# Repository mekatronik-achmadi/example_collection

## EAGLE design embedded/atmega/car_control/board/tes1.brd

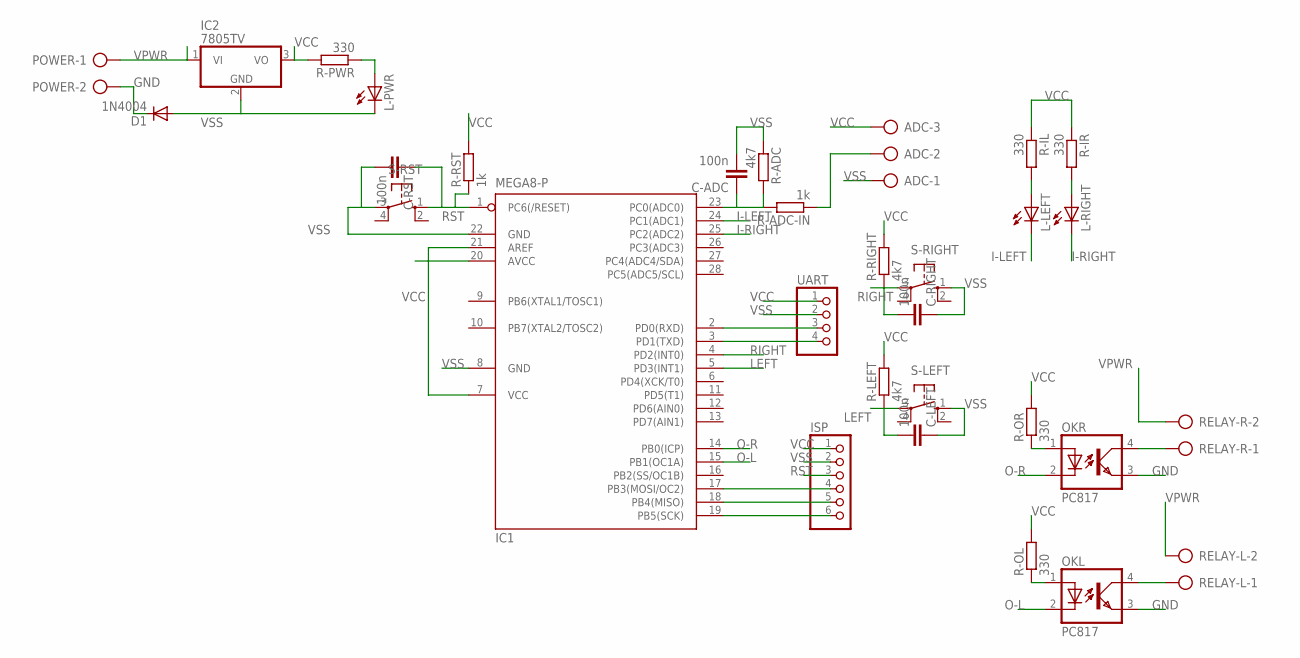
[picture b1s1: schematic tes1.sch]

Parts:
ADC: AK300/3
C-ADC: 100n; C050-024X044
C-LEFT: 100n; C050-024X044
C-RIGHT: 100n; C050-024X044
C-RST: 100n; C050-024X044
D1: 1N4004; DO41-10
IC1: MEGA8-P; DIL28-3
IC2: 7805TV; TO220V
ISP: PINHD-1X6; 1X06
L-LEFT: LED3MM
L-PWR: LED3MM
L-RIGHT: LED3MM
OKL: PC817; DIL04
OKR: PC817; DIL04
POWER: AK300/2
R-ADC: 4k7; 0204/7
R-ADC-IN: 1k; 0204/7
R-IL: 330; 0204/7
R-IR: 330; 0204/7
R-LEFT: 4k7; 0204/7
R-OL: 330; 0204/7
R-OR: 330; 0204/7
R-PWR: 330; 0204/7
R-RIGHT: 4k7; 0204/7
R-RST: 1k; 0204/7
RELAY-L: AK300/2
RELAY-R: AK300/2
S-LEFT: 10-XX; B3F-10XX
S-RIGHT: 10-XX; B3F-10XX
S-RST: 10-XX; B3F-10XX
UART: PINHD-1X4; 1X04

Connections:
GND: D1.C, OKL.3 (EMIT), OKR.3 (EMIT), POWER.2
I-LEFT: IC1.24 (PC1(ADC1)), L-LEFT.K (C)
I-RIGHT: IC1.25 (PC2(ADC2)), L-RIGHT.K (C)
LEFT: C-LEFT.2, IC1.5 (PD3(INT1)), R-LEFT.1, S-LEFT.3
unnamed: ADC.2, R-ADC-IN.1
unnamed: C-ADC.1, IC1.23 (PC0(ADC0)), R-ADC.2, R-ADC-IN.2
unnamed: IC1.3 (PD1(TXD)), UART.4
unnamed: IC1.2 (PD0(RXD)), UART.3
unnamed: L-PWR.A, R-PWR.1
unnamed: OKR.1 (A), R-OR.1
unnamed: OKL.1 (A), R-OL.1
unnamed: OKR.4 (COL), RELAY-R.1
unnamed: OKL.4 (COL), RELAY-L.1
unnamed: IC1.19 (PB5(SCK)), ISP.6
unnamed: IC1.18 (PB4(MISO)), ISP.5
unnamed: IC1.17 (PB3(MOSI/OC2)), ISP.4
unnamed: L-LEFT.A, R-IL.2
unnamed: L-RIGHT.A, R-IR.2
O-L: IC1.15 (PB1(OC1A)), OKL.2 (C)
O-R: IC1.14 (PB0(ICP)), OKR.2 (C)
RIGHT: C-RIGHT.2, IC1.4 (PD2(INT0)), R-RIGHT.1, S-RIGHT.3
RST: C-RST.1, IC1.1 (PC6(/RESET)), ISP.3, R-RST.1, S-RST.1 (S)
VCC: ADC.3, IC1.7 (VCC), IC1.20 (AVCC), IC1.21 (AREF), IC2.3 (VO), ISP.1, R-IL.1, R-IR.1, R-LEFT.2, R-OL.2, R-OR.2, R-PWR.2, R-RIGHT.2, R-RST.2, UART.1
VPWR: IC2.1 (VI), POWER.1, RELAY-L.2, RELAY-R.2
VSS: ADC.1, C-ADC.2, C-LEFT.1, C-RIGHT.1, C-RST.2, D1.A, IC1.8 (GND), IC1.22 (GND), IC2.2 (GND), ISP.2, L-PWR.K (C), R-ADC.1, S-LEFT.1 (S), S-RIGHT.1 (S), S-RST.3, UART.2

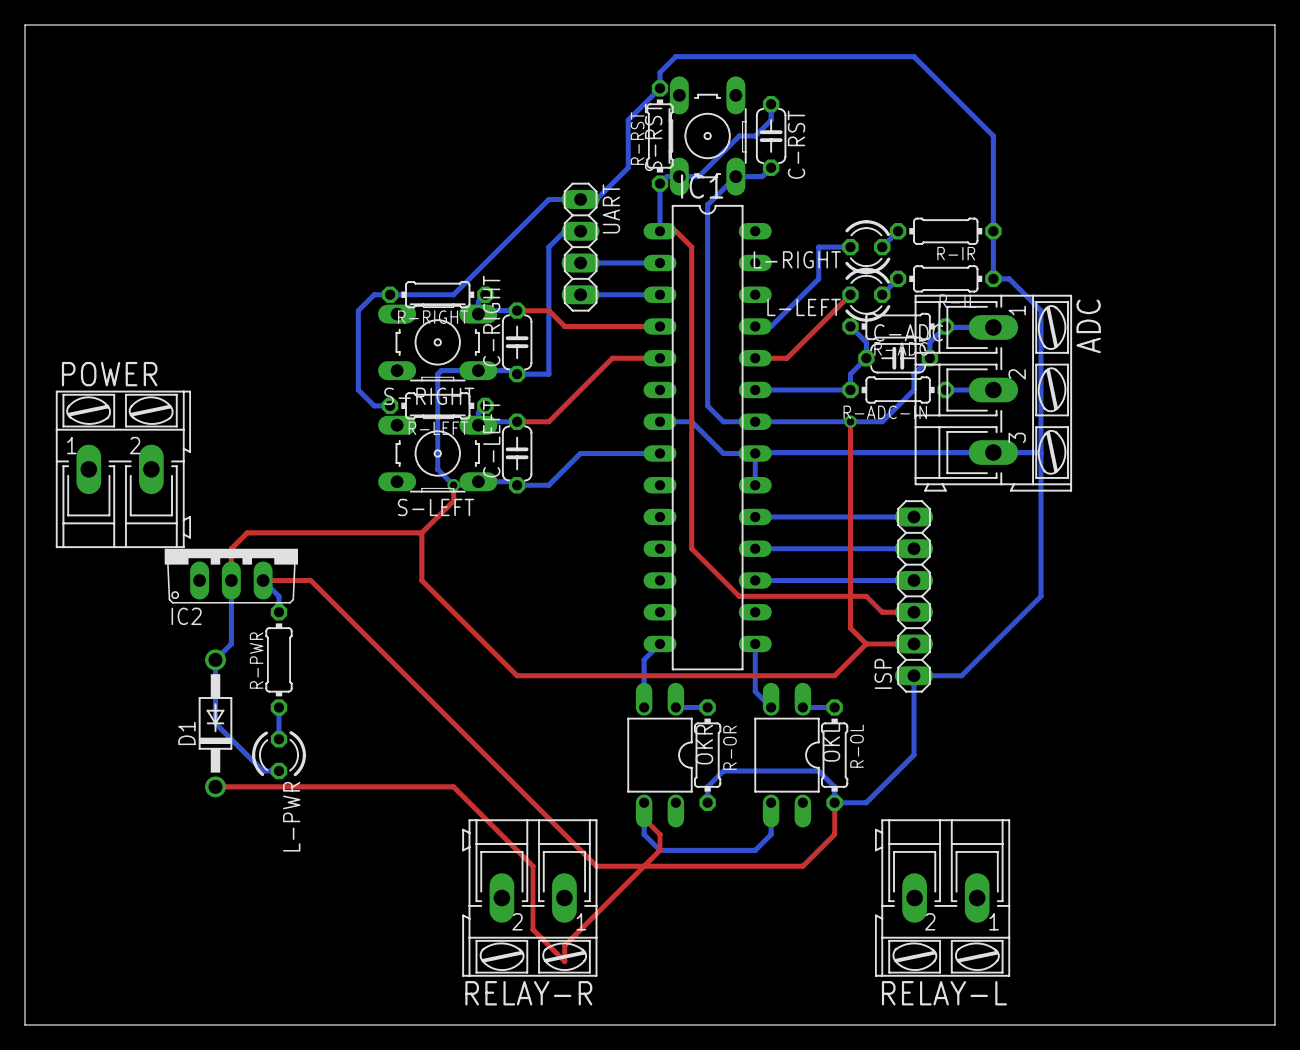
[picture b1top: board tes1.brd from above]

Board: 2 copper layers, 100.0 x 80.0 mm, 31 parts (0 on the bottom side), 25 nets.

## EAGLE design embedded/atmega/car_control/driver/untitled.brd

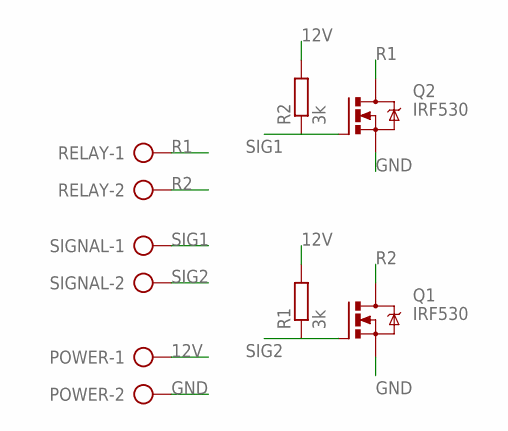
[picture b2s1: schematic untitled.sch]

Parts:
POWER: AK300/2
Q1, Q2: IRF530; TO220BV
R1, R2: 3k; 0204/7
RELAY: AK300/2
SIGNAL: AK300/2

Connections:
12V: POWER.1, R1.2, R2.2
GND: POWER.2, Q1.S, Q2.S
R1: Q2.D, RELAY.1
R2: Q1.D, RELAY.2
SIG1: Q2.G, R2.1, SIGNAL.1
SIG2: Q1.G, R1.1, SIGNAL.2

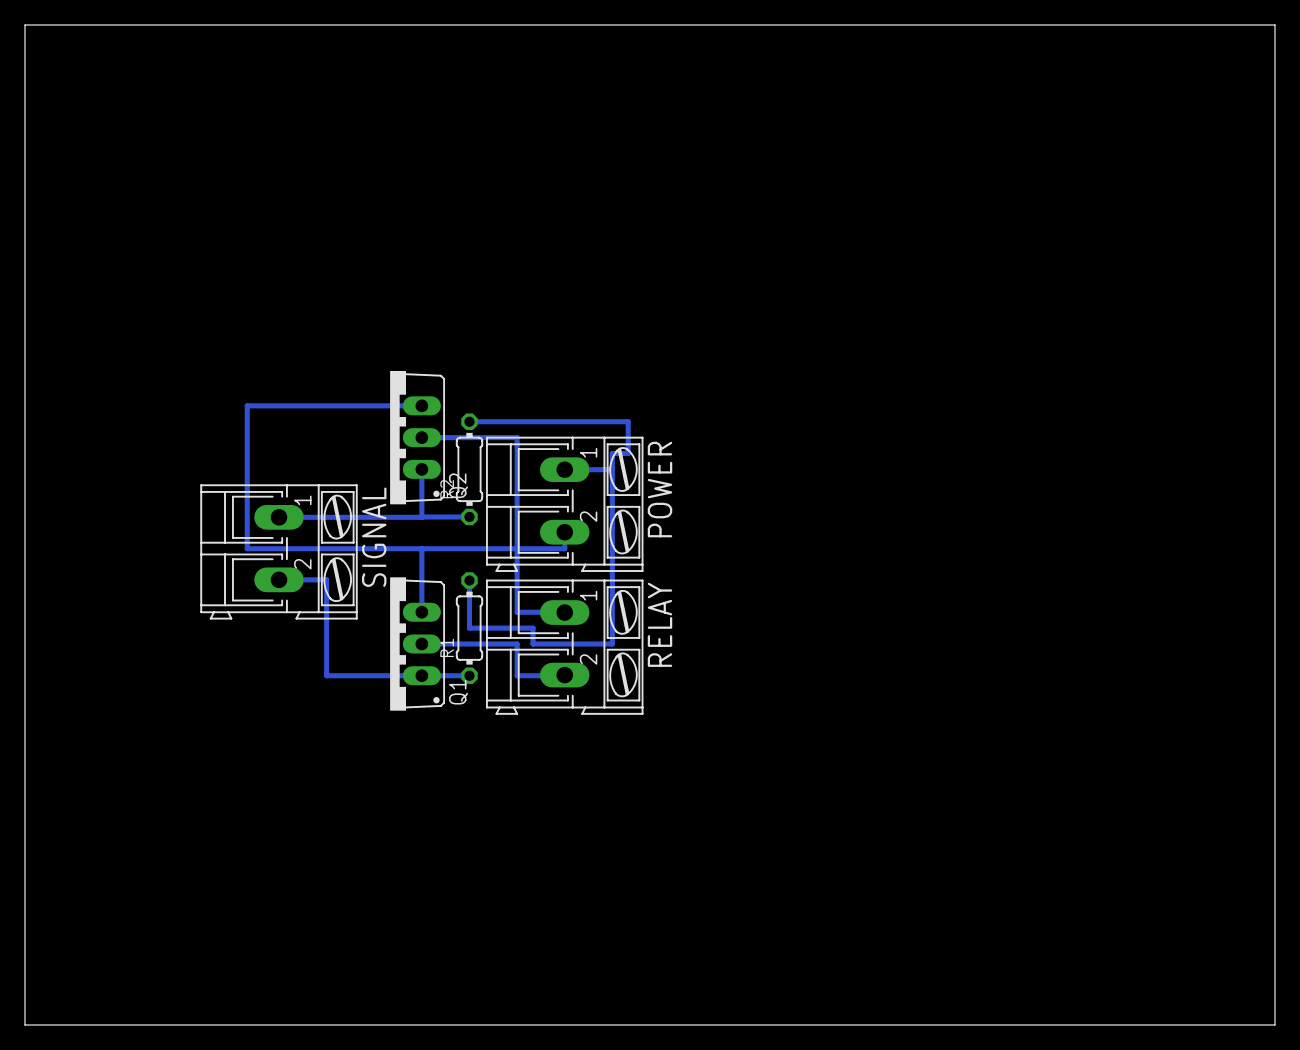
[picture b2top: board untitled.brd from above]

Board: 2 copper layers, 100.0 x 80.0 mm, 7 parts (0 on the bottom side), 6 nets.

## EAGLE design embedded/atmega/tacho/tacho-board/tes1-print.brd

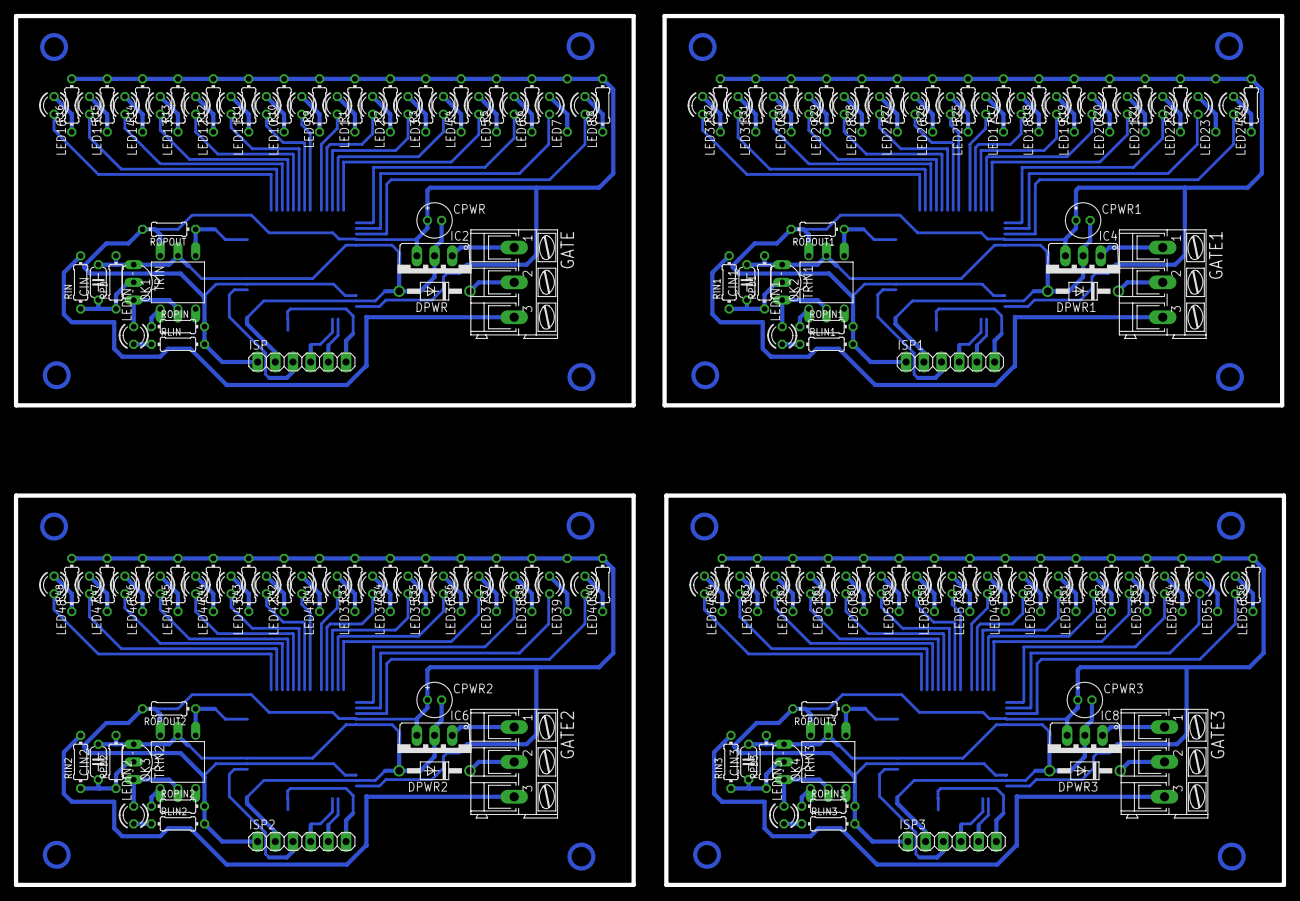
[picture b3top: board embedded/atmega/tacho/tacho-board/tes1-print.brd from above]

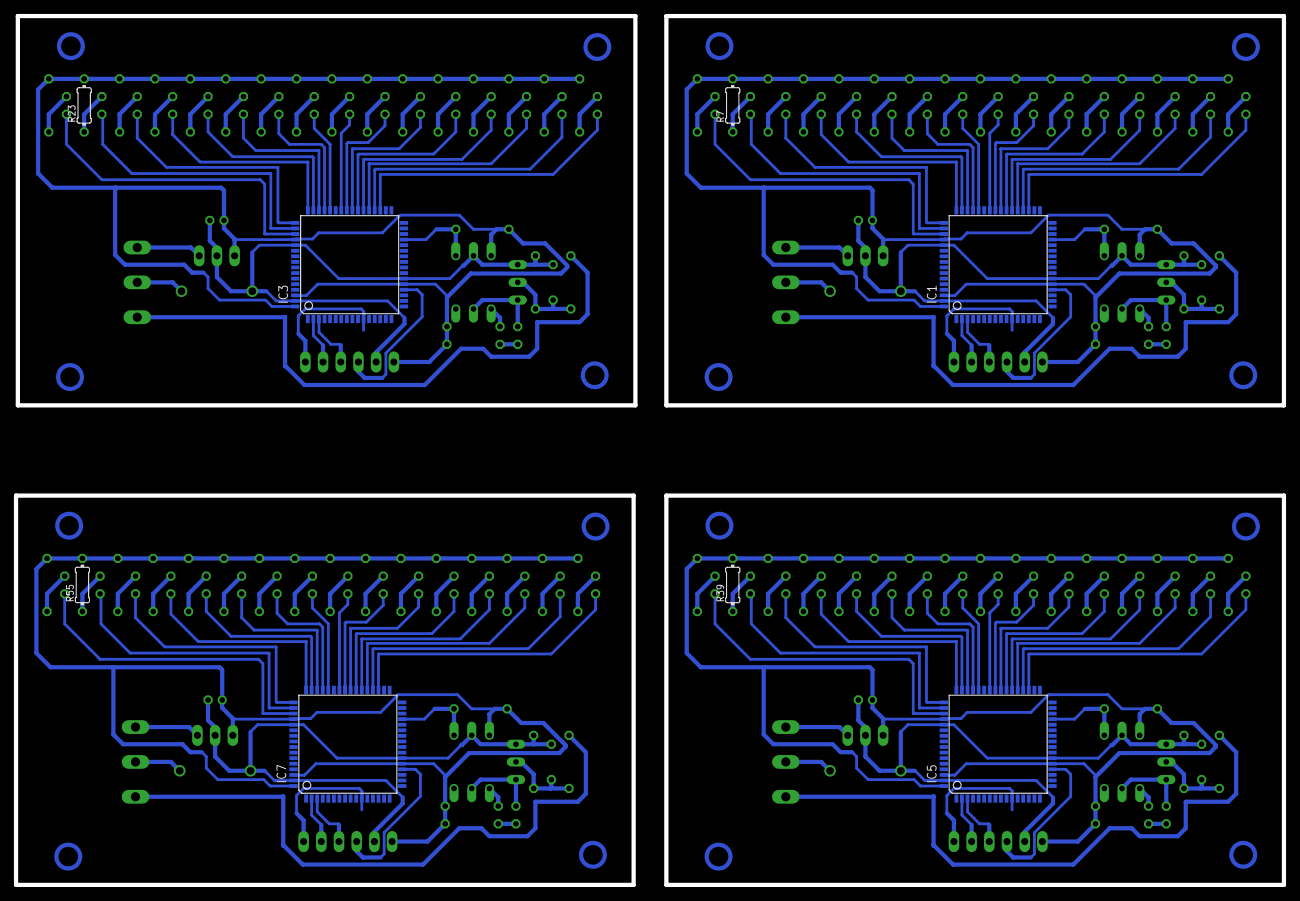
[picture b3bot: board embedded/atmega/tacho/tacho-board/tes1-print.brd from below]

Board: 2 copper layers, 182.0 x 124.7 mm, 188 parts (8 on the bottom side), 184 nets.

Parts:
CIN, CIN1, CIN2, CIN3: 100n; C050-024X044
CPWR, CPWR1, CPWR2, CPWR3: 100u; E2-5
DPWR, DPWR1, DPWR2, DPWR3: 1N4004; DO41-10
GATE, GATE1, GATE2, GATE3: AK300/3
IC1, IC3, IC5, IC7: MEGA128-A; TQFP64
IC2, IC4, IC6, IC8: 7805TV; TO220V
ISP, ISP1, ISP2, ISP3: 1X06
LED1, LED2, LED3, LED4, LED5, LED6, LED7, LED8, LED9, LED10, LED11, LED12, LED13, LED14, LED15, LED16, LED17, LED18, LED19, LED20, LED21, LED22, LED23, LED24, LED25, LED26, LED27, LED28, LED29, LED30, LED31, LED32, LED33, LED34, LED35, LED36, LED37, LED38, LED39, LED40, LED41, LED42, LED43, LED44, LED45, LED46, LED47, LED48, LED49, LED50, LED51, LED52, LED53, LED54, LED55, LED56, LED57, LED58, LED59, LED60, LED61, LED62, LED63, LED64: LED3MM
LEDIN, LEDIN1, LEDIN2, LEDIN3: LED3MM
OK1, OK2, OK3, OK4: H11L1M; DIL06
R1, R2, R3, R4, R5, R6, R7, R8, R9, R10, R11, R12, R13, R14, R15, R16, R17, R18, R19, R20, R21, R22, R23, R24, R25, R26, R27, R28, R29, R30, R31, R32, R33, R34, R35, R36, R37, R38, R39, R40, R41, R42, R43, R44, R45, R46, R47, R48, R49, R50, R51, R52, R53, R54, R55, R56, R57, R58, R59, R60, R61, R62, R63, R64: 220; 0204/7
RIN, RIN1, RIN2, RIN3: 1k; 0204/7
RLIN, RLIN1, RLIN2, RLIN3: 220; 0204/7
ROPIN, ROPIN1, ROPIN2, ROPIN3: 220; 0204/7
ROPOUT, ROPOUT1, ROPOUT2, ROPOUT3: 4k7; 0204/7
RPD, RPD1, RPD2, RPD3: 4k7; 0204/7
TRIN, TRIN1, TRIN2, TRIN3: TO92-EBC

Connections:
FIN: IC1.29, OK1.4, ROPOUT.1
FIN1: IC3.29, OK2.4, ROPOUT1.1
FIN2: IC5.29, OK3.4, ROPOUT2.1
FIN3: IC7.29, OK4.4, ROPOUT3.1
GND: CIN.2, CPWR.-, DPWR.A, IC1.22, IC1.53, IC1.63, IC2.2, ISP.2, OK1.5, RPD.2, TRIN.E
GND1: CIN1.2, CPWR1.-, DPWR1.A, IC3.22, IC3.53, IC3.63, IC4.2, ISP1.2, OK2.5, RPD1.2, TRIN1.E
GND2: CIN2.2, CPWR2.-, DPWR2.A, IC5.22, IC5.53, IC5.63, IC6.2, ISP2.2, OK3.5, RPD2.2, TRIN2.E
GND3: CIN3.2, CPWR3.-, DPWR3.A, IC7.22, IC7.53, IC7.63, IC8.2, ISP3.2, OK4.5, RPD3.2, TRIN3.E
IN: GATE.3, RIN.2
IN1: GATE1.3, RIN1.2
IN2: GATE2.3, RIN2.2
IN3: GATE3.3, RIN3.2
MISO: IC1.3, ISP.4
MISO1: IC3.3, ISP1.4
MISO2: IC5.3, ISP2.4
MISO3: IC7.3, ISP3.4
MOSI: IC1.2, ISP.5
MOSI1: IC3.2, ISP1.5
MOSI2: IC5.2, ISP2.5
MOSI3: IC7.2, ISP3.5
unnamed: LED2.A, R2.1
unnamed: LED17.A, R17.1
unnamed: LED18.A, R18.1
unnamed: LED19.A, R19.1
unnamed: LED20.A, R20.1
unnamed: LED21.A, R21.1
unnamed: LED3.A, R3.1
unnamed: LED1.A, R1.1
unnamed: LED4.A, R4.1
unnamed: LED22.A, R22.1
unnamed: LED5.A, R5.1
unnamed: LED6.A, R6.1
unnamed: LED7.A, R7.1
unnamed: LED8.A, R8.1
unnamed: LED9.A, R9.1
unnamed: LED10.A, R10.1
unnamed: LED11.A, R11.1
unnamed: LED12.A, R12.1
unnamed: LED13.A, R13.1
unnamed: LED14.A, R14.1
unnamed: LED15.A, R15.1
unnamed: LED16.A, R16.1
unnamed: LED23.A, R23.1
unnamed: LED24.A, R24.1
unnamed: LED25.A, R25.1
unnamed: LED26.A, R26.1
unnamed: LED27.A, R27.1
unnamed: LED28.A, R28.1
unnamed: LED29.A, R29.1
unnamed: LED30.A, R30.1
unnamed: LED31.A, R31.1
unnamed: LED32.A, R32.1
unnamed: DPWR1.C, GATE1.2
unnamed: GATE1.1, IC4.1
unnamed: CIN1.1, RIN1.1, RPD1.1, TRIN1.B
unnamed: LEDIN1.K, OK2.2, TRIN1.C
unnamed: OK2.1, ROPIN1.1
unnamed: LEDIN1.A, RLIN1.1
unnamed: LED33.A, R33.1
unnamed: LED34.A, R34.1
unnamed: LED35.A, R35.1
unnamed: LED36.A, R36.1
unnamed: DPWR.C, GATE.2
unnamed: GATE.1, IC2.1
unnamed: LED37.A, R37.1
unnamed: LED38.A, R38.1
unnamed: CIN.1, RIN.1, RPD.1, TRIN.B
unnamed: LEDIN.K, OK1.2, TRIN.C
unnamed: OK1.1, ROPIN.1
unnamed: LEDIN.A, RLIN.1
unnamed: LED39.A, R39.1
unnamed: LED40.A, R40.1
unnamed: LED41.A, R41.1
unnamed: LED42.A, R42.1
unnamed: LED43.A, R43.1
unnamed: LED44.A, R44.1
unnamed: LED45.A, R45.1
unnamed: LED46.A, R46.1
unnamed: LED47.A, R47.1
unnamed: LED48.A, R48.1
unnamed: DPWR2.C, GATE2.2
unnamed: GATE2.1, IC6.1
unnamed: CIN2.1, RIN2.1, RPD2.1, TRIN2.B
unnamed: LEDIN2.K, OK3.2, TRIN2.C
unnamed: OK3.1, ROPIN2.1
unnamed: LEDIN2.A, RLIN2.1
unnamed: LED49.A, R49.1
unnamed: LED50.A, R50.1
unnamed: LED51.A, R51.1
unnamed: LED52.A, R52.1
unnamed: LED53.A, R53.1
unnamed: LED54.A, R54.1
unnamed: LED55.A, R55.1
unnamed: LED56.A, R56.1
unnamed: LED57.A, R57.1
unnamed: LED58.A, R58.1
unnamed: LED59.A, R59.1
unnamed: LED60.A, R60.1
unnamed: LED61.A, R61.1
unnamed: LED62.A, R62.1
unnamed: LED63.A, R63.1
unnamed: LED64.A, R64.1
unnamed: DPWR3.C, GATE3.2
unnamed: GATE3.1, IC8.1
unnamed: CIN3.1, RIN3.1, RPD3.1, TRIN3.B
unnamed: LEDIN3.K, OK4.2, TRIN3.C
unnamed: OK4.1, ROPIN3.1
unnamed: LEDIN3.A, RLIN3.1
P1: IC1.44, LED1.K
P2: IC1.45, LED2.K
P3: IC1.46, LED3.K
P4: IC1.47, LED4.K
P5: IC1.48, LED5.K
P6: IC1.49, LED6.K
P7: IC1.50, LED7.K
P8: IC1.51, LED8.K
P9: IC1.42, LED9.K
P10: IC1.41, LED10.K
P11: IC1.40, LED11.K
P12: IC1.39, LED12.K
P13: IC1.38, LED13.K
P14: IC1.37, LED14.K
P15: IC1.36, LED15.K
P16: IC1.35, LED16.K
P17: IC3.44, LED17.K
P18: IC3.45, LED18.K
P19: IC3.46, LED19.K
P20: IC3.47, LED20.K
P21: IC3.48, LED21.K
P22: IC3.49, LED22.K
P23: IC3.50, LED23.K
P24: IC3.51, LED24.K
P25: IC3.35, LED32.K
P26: IC3.36, LED31.K
P27: IC3.37, LED30.K
P28: IC3.38, LED29.K
P29: IC3.39, LED28.K
P30: IC3.40, LED27.K
P31: IC3.41, LED26.K
P32: IC3.42, LED25.K
P33: IC5.44, LED33.K
P34: IC5.45, LED34.K
P35: IC5.46, LED35.K
P36: IC5.47, LED36.K
P37: IC5.48, LED37.K
P38: IC5.49, LED38.K
P39: IC5.50, LED39.K
P40: IC5.51, LED40.K
P41: IC5.35, LED48.K
P42: IC5.36, LED47.K
P43: IC5.37, LED46.K
P44: IC5.38, LED45.K
P45: IC5.39, LED44.K
P46: IC5.40, LED43.K
P47: IC5.41, LED42.K
P48: IC5.42, LED41.K
P49: IC7.44, LED49.K
P50: IC7.45, LED50.K
P51: IC7.46, LED51.K
P52: IC7.47, LED52.K
P53: IC7.48, LED53.K
P54: IC7.49, LED54.K
P55: IC7.50, LED55.K
P56: IC7.51, LED56.K
P57: IC7.35, LED64.K
P58: IC7.36, LED63.K
P59: IC7.37, LED62.K
P60: IC7.38, LED61.K
P61: IC7.39, LED60.K
P62: IC7.40, LED59.K
P63: IC7.41, LED58.K
P64: IC7.42, LED57.K
RST: IC1.20, ISP.3
RST1: IC3.20, ISP1.3
RST2: IC5.20, ISP2.3
RST3: IC7.20, ISP3.3
SCK: IC1.11, ISP.6
SCK1: IC3.11, ISP1.6
SCK2: IC5.11, ISP2.6
SCK3: IC7.11, ISP3.6
VCC: CPWR.+, IC1.21, IC1.52, IC1.62, IC1.64, IC2.3, ISP.1, OK1.6, R1.2, R2.2, R3.2, R4.2, R5.2, R6.2, R7.2, R8.2, R9.2, R10.2, R11.2, R12.2, R13.2, R14.2, R15.2, R16.2, RLIN.2, ROPIN.2, ROPOUT.2
VCC1: CPWR1.+, IC3.21, IC3.52, IC3.62, IC3.64, IC4.3, ISP1.1, OK2.6, R17.2, R18.2, R19.2, R20.2, R21.2, R22.2, R23.2, R24.2, R25.2, R26.2, R27.2, R28.2, R29.2, R30.2, R31.2, R32.2, RLIN1.2, ROPIN1.2, ROPOUT1.2
VCC2: CPWR2.+, IC5.21, IC5.52, IC5.62, IC5.64, IC6.3, ISP2.1, OK3.6, R33.2, R34.2, R35.2, R36.2, R37.2, R38.2, R39.2, R40.2, R41.2, R42.2, R43.2, R44.2, R45.2, R46.2, R47.2, R48.2, RLIN2.2, ROPIN2.2, ROPOUT2.2
VCC3: CPWR3.+, IC7.21, IC7.52, IC7.62, IC7.64, IC8.3, ISP3.1, OK4.6, R49.2, R50.2, R51.2, R52.2, R53.2, R54.2, R55.2, R56.2, R57.2, R58.2, R59.2, R60.2, R61.2, R62.2, R63.2, R64.2, RLIN3.2, ROPIN3.2, ROPOUT3.2

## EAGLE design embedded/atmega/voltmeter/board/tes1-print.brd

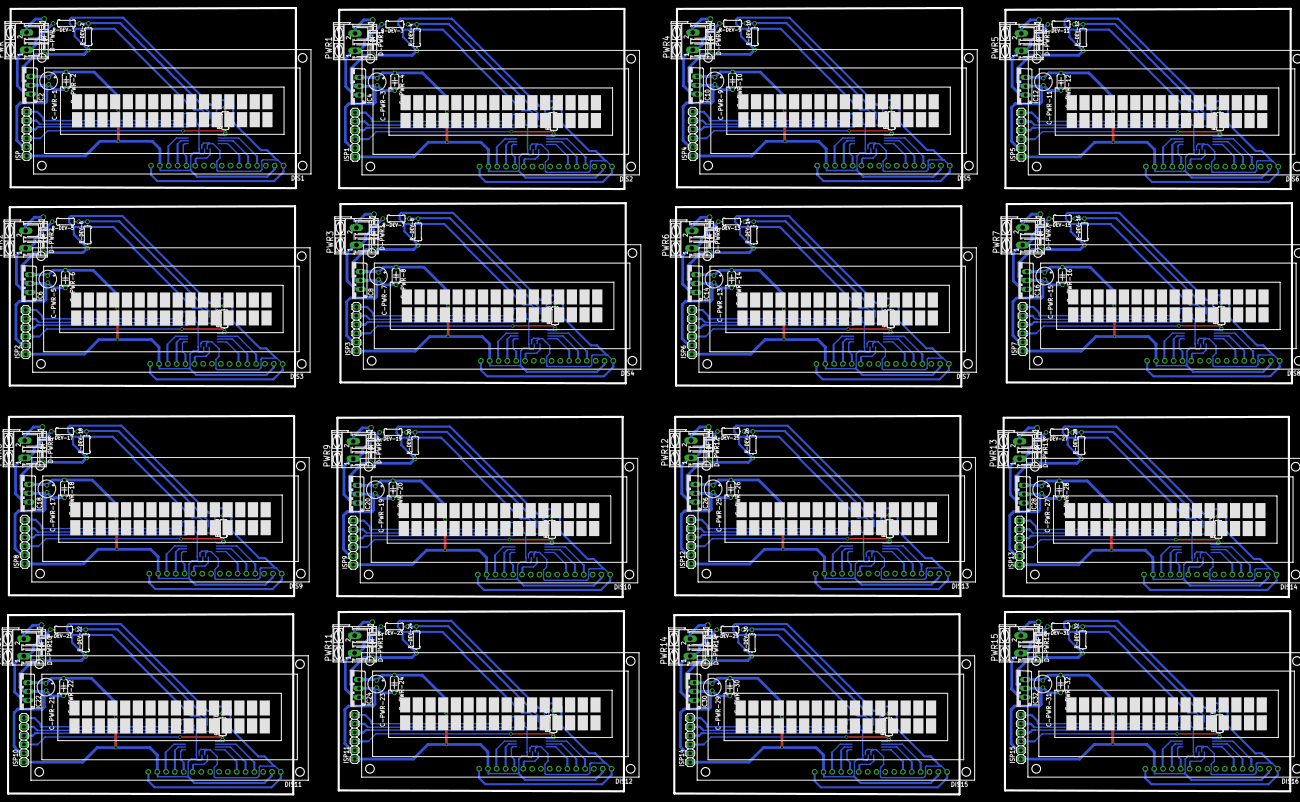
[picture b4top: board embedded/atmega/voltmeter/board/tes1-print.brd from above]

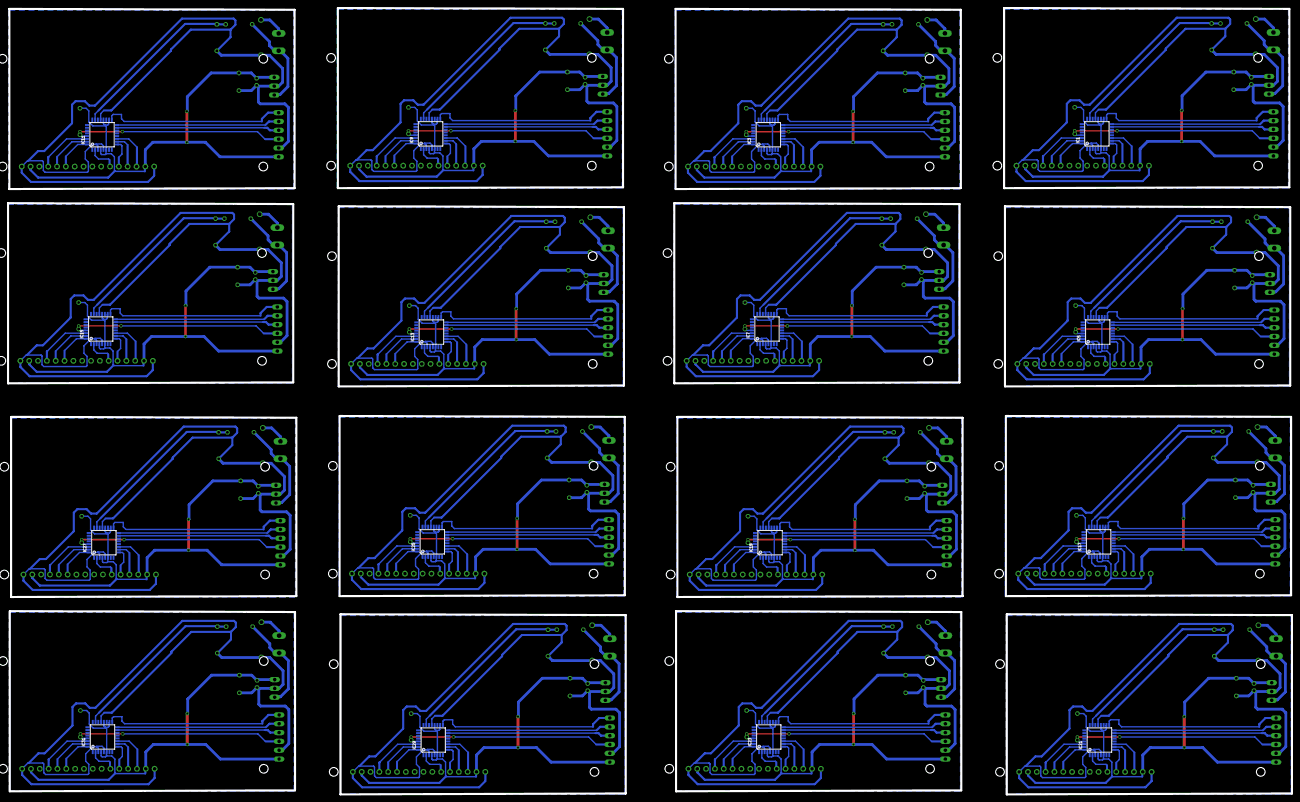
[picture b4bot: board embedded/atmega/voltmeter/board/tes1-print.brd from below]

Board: 2 copper layers, 369.3 x 226.2 mm, 176 parts (16 on the bottom side), 256 nets.

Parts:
C-PWR-1, C-PWR-3, C-PWR-5, C-PWR-7, C-PWR-9, C-PWR-11, C-PWR-13, C-PWR-15, C-PWR-17, C-PWR-19, C-PWR-21, C-PWR-23, C-PWR-25, C-PWR-27, C-PWR-29, C-PWR-31: E2-5
C-PWR-2, C-PWR-4, C-PWR-6, C-PWR-8, C-PWR-10, C-PWR-12, C-PWR-14, C-PWR-16, C-PWR-18, C-PWR-20, C-PWR-22, C-PWR-24, C-PWR-26, C-PWR-28, C-PWR-30, C-PWR-32: C050-024X044
D-PWR, D-PWR1, D-PWR2, D-PWR3, D-PWR4, D-PWR5, D-PWR6, D-PWR7, D-PWR8, D-PWR9, D-PWR10, D-PWR11, D-PWR12, D-PWR13, D-PWR14, D-PWR15: 1N4004; DO41-10
DIS1, DIS2, DIS3, DIS4, DIS5, DIS6, DIS7, DIS8, DIS9, DIS10, DIS11, DIS12, DIS13, DIS14, DIS15, DIS16: TUXGR_16X2_R2
IC1, IC3, IC5, IC7, IC9, IC11, IC13, IC15, IC17, IC19, IC21, IC23, IC25, IC27, IC29, IC31: MEGA8-AI; TQFP32-08
IC2, IC4, IC6, IC8, IC10, IC12, IC14, IC16, IC18, IC20, IC22, IC24, IC26, IC28, IC30, IC32: 7805TV; TO220V
ISP, ISP1, ISP2, ISP3, ISP4, ISP5, ISP6, ISP7, ISP8, ISP9, ISP10, ISP11, ISP12, ISP13, ISP14, ISP15: 1X06
PWR, PWR1, PWR2, PWR3, PWR4, PWR5, PWR6, PWR7, PWR8, PWR9, PWR10, PWR11, PWR12, PWR13, PWR14, PWR15: AK300/2
R-DEV-1, R-DEV-2, R-DEV-3, R-DEV-4, R-DEV-5, R-DEV-6, R-DEV-7, R-DEV-8, R-DEV-9, R-DEV-10, R-DEV-11, R-DEV-12, R-DEV-13, R-DEV-14, R-DEV-15, R-DEV-16, R-DEV-17, R-DEV-18, R-DEV-19, R-DEV-20, R-DEV-21, R-DEV-22, R-DEV-23, R-DEV-24, R-DEV-25, R-DEV-26, R-DEV-27, R-DEV-28, R-DEV-29, R-DEV-30, R-DEV-31, R-DEV-32: 0204/7
R-RST, R-RST1, R-RST2, R-RST3, R-RST4, R-RST5, R-RST6, R-RST7, R-RST8, R-RST9, R-RST10, R-RST11, R-RST12, R-RST13, R-RST14, R-RST15: 0204/7

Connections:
D1: DIS2.11, IC3.2
D2: DIS2.12, IC3.9
D3: DIS2.13, IC3.10
D4: DIS1.11, IC1.2
D5: DIS1.12, IC1.9
D6: DIS1.13, IC1.10
D7: DIS1.14, IC1.11
D8: DIS2.14, IC3.11
D9: DIS3.11, IC5.2
D10: DIS3.12, IC5.9
D11: DIS3.13, IC5.10
D12: DIS3.14, IC5.11
D13: DIS4.11, IC7.2
D14: DIS4.12, IC7.9
D15: DIS4.13, IC7.10
D16: DIS4.14, IC7.11
D17: DIS5.11, IC9.2
D18: DIS5.12, IC9.9
D19: DIS5.13, IC9.10
D20: DIS5.14, IC9.11
D21: DIS6.11, IC11.2
D22: DIS6.12, IC11.9
D23: DIS6.13, IC11.10
D24: DIS6.14, IC11.11
D25: DIS7.11, IC13.2
D26: DIS7.12, IC13.9
D27: DIS7.13, IC13.10
D28: DIS7.14, IC13.11
D29: DIS8.11, IC15.2
D30: DIS8.12, IC15.9
D31: DIS8.13, IC15.10
D32: DIS8.14, IC15.11
D33: DIS9.11, IC17.2
D34: DIS9.12, IC17.9
D35: DIS9.13, IC17.10
D36: DIS9.14, IC17.11
D37: DIS10.11, IC19.2
D38: DIS10.12, IC19.9
D39: DIS10.13, IC19.10
D40: DIS10.14, IC19.11
D41: DIS11.11, IC21.2
D42: DIS11.12, IC21.9
D43: DIS11.13, IC21.10
D44: DIS11.14, IC21.11
D45: DIS12.11, IC23.2
D46: DIS12.12, IC23.9
D47: DIS12.13, IC23.10
D48: DIS12.14, IC23.11
D49: DIS13.11, IC25.2
D50: DIS13.12, IC25.9
D51: DIS13.13, IC25.10
D52: DIS13.14, IC25.11
D53: DIS14.11, IC27.2
D54: DIS14.12, IC27.9
D55: DIS14.13, IC27.10
D56: DIS14.14, IC27.11
D57: DIS15.11, IC29.2
D58: DIS15.12, IC29.9
D59: DIS15.13, IC29.10
D60: DIS15.14, IC29.11
D61: DIS16.11, IC31.2
D62: DIS16.12, IC31.9
D63: DIS16.13, IC31.10
D64: DIS16.14, IC31.11
EN: DIS1.6, IC1.32
EN1: DIS2.6, IC3.32
EN2: DIS3.6, IC5.32
EN3: DIS4.6, IC7.32
EN4: DIS5.6, IC9.32
EN5: DIS6.6, IC11.32
EN6: DIS7.6, IC13.32
EN7: DIS8.6, IC15.32
EN8: DIS9.6, IC17.32
EN9: DIS10.6, IC19.32
EN10: DIS11.6, IC21.32
EN11: DIS12.6, IC23.32
EN12: DIS13.6, IC25.32
EN13: DIS14.6, IC27.32
EN14: DIS15.6, IC29.32
EN15: DIS16.6, IC31.32
GND: C-PWR-1.-, C-PWR-2.2, D-PWR.A, DIS1.1, DIS1.16, IC1.3, IC1.5, IC1.21, IC2.2, ISP.2, R-DEV-2.1
GND1: C-PWR-3.-, C-PWR-4.2, D-PWR1.A, DIS2.1, DIS2.16, IC3.3, IC3.5, IC3.21, IC4.2, ISP1.2, R-DEV-4.1
GND2: C-PWR-5.-, C-PWR-6.2, D-PWR2.A, DIS3.1, DIS3.16, IC5.3, IC5.5, IC5.21, IC6.2, ISP2.2, R-DEV-6.1
GND3: C-PWR-7.-, C-PWR-8.2, D-PWR3.A, DIS4.1, DIS4.16, IC7.3, IC7.5, IC7.21, IC8.2, ISP3.2, R-DEV-8.1
GND4: C-PWR-9.-, C-PWR-10.2, D-PWR4.A, DIS5.1, DIS5.16, IC9.3, IC9.5, IC9.21, IC10.2, ISP4.2, R-DEV-10.1
GND5: C-PWR-11.-, C-PWR-12.2, D-PWR5.A, DIS6.1, DIS6.16, IC11.3, IC11.5, IC11.21, IC12.2, ISP5.2, R-DEV-12.1
GND6: C-PWR-13.-, C-PWR-14.2, D-PWR6.A, DIS7.1, DIS7.16, IC13.3, IC13.5, IC13.21, IC14.2, ISP6.2, R-DEV-14.1
GND7: C-PWR-15.-, C-PWR-16.2, D-PWR7.A, DIS8.1, DIS8.16, IC15.3, IC15.5, IC15.21, IC16.2, ISP7.2, R-DEV-16.1
GND8: C-PWR-17.-, C-PWR-18.2, D-PWR8.A, DIS9.1, DIS9.16, IC17.3, IC17.5, IC17.21, IC18.2, ISP8.2, R-DEV-18.1
GND9: C-PWR-19.-, C-PWR-20.2, D-PWR9.A, DIS10.1, DIS10.16, IC19.3, IC19.5, IC19.21, IC20.2, ISP9.2, R-DEV-20.1
GND10: C-PWR-21.-, C-PWR-22.2, D-PWR10.A, DIS11.1, DIS11.16, IC21.3, IC21.5, IC21.21, IC22.2, ISP10.2, R-DEV-22.1
GND11: C-PWR-23.-, C-PWR-24.2, D-PWR11.A, DIS12.1, DIS12.16, IC23.3, IC23.5, IC23.21, IC24.2, ISP11.2, R-DEV-24.1
GND12: C-PWR-25.-, C-PWR-26.2, D-PWR12.A, DIS13.1, DIS13.16, IC25.3, IC25.5, IC25.21, IC26.2, ISP12.2, R-DEV-26.1
GND13: C-PWR-27.-, C-PWR-28.2, D-PWR13.A, DIS14.1, DIS14.16, IC27.3, IC27.5, IC27.21, IC28.2, ISP13.2, R-DEV-28.1
GND14: C-PWR-29.-, C-PWR-30.2, D-PWR14.A, DIS15.1, DIS15.16, IC29.3, IC29.5, IC29.21, IC30.2, ISP14.2, R-DEV-30.1
GND15: C-PWR-31.-, C-PWR-32.2, D-PWR15.A, DIS16.1, DIS16.16, IC31.3, IC31.5, IC31.21, IC32.2, ISP15.2, R-DEV-32.1
IN: IC1.23, R-DEV-1.1, R-DEV-2.2
IN1: IC3.23, R-DEV-3.1, R-DEV-4.2
IN2: IC5.23, R-DEV-5.1, R-DEV-6.2
IN3: IC7.23, R-DEV-7.1, R-DEV-8.2
IN4: IC9.23, R-DEV-9.1, R-DEV-10.2
IN5: IC11.23, R-DEV-11.1, R-DEV-12.2
IN6: IC13.23, R-DEV-13.1, R-DEV-14.2
IN7: IC15.23, R-DEV-15.1, R-DEV-16.2
IN8: IC17.23, R-DEV-17.1, R-DEV-18.2
IN9: IC19.23, R-DEV-19.1, R-DEV-20.2
IN10: IC21.23, R-DEV-21.1, R-DEV-22.2
IN11: IC23.23, R-DEV-23.1, R-DEV-24.2
IN12: IC25.23, R-DEV-25.1, R-DEV-26.2
IN13: IC27.23, R-DEV-27.1, R-DEV-28.2
IN14: IC29.23, R-DEV-29.1, R-DEV-30.2
IN15: IC31.23, R-DEV-31.1, R-DEV-32.2
unnamed: IC3.17, ISP1.6
unnamed: IC3.16, ISP1.5
unnamed: IC3.15, ISP1.4
unnamed: IC5.17, ISP2.6
unnamed: IC5.16, ISP2.5
unnamed: IC5.15, ISP2.4
unnamed: IC7.17, ISP3.6
unnamed: IC7.16, ISP3.5
unnamed: IC7.15, ISP3.4
unnamed: IC9.17, ISP4.6
unnamed: IC1.17, ISP.6
unnamed: IC1.16, ISP.5
unnamed: IC1.15, ISP.4
unnamed: IC9.16, ISP4.5
unnamed: IC9.15, ISP4.4
unnamed: IC11.17, ISP5.6
unnamed: IC11.16, ISP5.5
unnamed: IC11.15, ISP5.4
unnamed: IC13.17, ISP6.6
unnamed: IC13.16, ISP6.5
unnamed: IC13.15, ISP6.4
unnamed: IC15.17, ISP7.6
unnamed: IC15.16, ISP7.5
unnamed: IC15.15, ISP7.4
unnamed: IC17.17, ISP8.6
unnamed: IC17.16, ISP8.5
unnamed: IC17.15, ISP8.4
unnamed: IC19.17, ISP9.6
unnamed: IC19.16, ISP9.5
unnamed: IC19.15, ISP9.4
unnamed: IC21.17, ISP10.6
unnamed: IC21.16, ISP10.5
unnamed: IC21.15, ISP10.4
unnamed: IC23.17, ISP11.6
unnamed: IC23.16, ISP11.5
unnamed: IC23.15, ISP11.4
unnamed: IC25.17, ISP12.6
unnamed: IC25.16, ISP12.5
unnamed: IC25.15, ISP12.4
unnamed: IC27.17, ISP13.6
unnamed: IC27.16, ISP13.5
unnamed: IC27.15, ISP13.4
unnamed: IC29.17, ISP14.6
unnamed: IC29.16, ISP14.5
unnamed: IC29.15, ISP14.4
unnamed: IC31.17, ISP15.6
unnamed: IC31.16, ISP15.5
unnamed: IC31.15, ISP15.4
RS: DIS1.4, IC1.30
RS1: DIS2.4, IC3.30
RS2: DIS3.4, IC5.30
RS3: DIS4.4, IC7.30
RS4: DIS5.4, IC9.30
RS5: DIS6.4, IC11.30
RS6: DIS7.4, IC13.30
RS7: DIS8.4, IC15.30
RS8: DIS9.4, IC17.30
RS9: DIS10.4, IC19.30
RS10: DIS11.4, IC21.30
RS11: DIS12.4, IC23.30
RS12: DIS13.4, IC25.30
RS13: DIS14.4, IC27.30
RS14: DIS15.4, IC29.30
RS15: DIS16.4, IC31.30
RST: IC1.29, ISP.3, R-RST.1
RST1: IC3.29, ISP1.3, R-RST1.1
RST2: IC5.29, ISP2.3, R-RST2.1
RST3: IC7.29, ISP3.3, R-RST3.1
RST4: IC9.29, ISP4.3, R-RST4.1
RST5: IC11.29, ISP5.3, R-RST5.1
RST6: IC13.29, ISP6.3, R-RST6.1
RST7: IC15.29, ISP7.3, R-RST7.1
RST8: IC17.29, ISP8.3, R-RST8.1
RST9: IC19.29, ISP9.3, R-RST9.1
RST10: IC21.29, ISP10.3, R-RST10.1
RST11: IC23.29, ISP11.3, R-RST11.1
RST12: IC25.29, ISP12.3, R-RST12.1
RST13: IC27.29, ISP13.3, R-RST13.1
RST14: IC29.29, ISP14.3, R-RST14.1
RST15: IC31.29, ISP15.3, R-RST15.1
RW: DIS1.5, IC1.31
RW1: DIS2.5, IC3.31
RW2: DIS3.5, IC5.31
RW3: DIS4.5, IC7.31
RW4: DIS5.5, IC9.31
RW5: DIS6.5, IC11.31
RW6: DIS7.5, IC13.31
RW7: DIS8.5, IC15.31
RW8: DIS9.5, IC17.31
RW9: DIS10.5, IC19.31
RW10: DIS11.5, IC21.31
RW11: DIS12.5, IC23.31
RW12: DIS13.5, IC25.31
RW13: DIS14.5, IC27.31
RW14: DIS15.5, IC29.31
RW15: DIS16.5, IC31.31
V0: D-PWR.C, PWR.2
V1: D-PWR1.C, PWR1.2
V2: IC4.1, PWR1.1, R-DEV-3.2
V3: D-PWR2.C, PWR2.2
V4: IC6.1, PWR2.1, R-DEV-5.2
V5: D-PWR3.C, PWR3.2
V6: IC8.1, PWR3.1, R-DEV-7.2
V7: D-PWR4.C, PWR4.2
V8: IC10.1, PWR4.1, R-DEV-9.2
V9: D-PWR5.C, PWR5.2
V10: IC12.1, PWR5.1, R-DEV-11.2
V11: D-PWR6.C, PWR6.2
V12: IC2.1, PWR.1, R-DEV-1.2
V13: IC14.1, PWR6.1, R-DEV-13.2
V14: D-PWR7.C, PWR7.2
V15: IC16.1, PWR7.1, R-DEV-15.2
V16: D-PWR8.C, PWR8.2
V17: IC18.1, PWR8.1, R-DEV-17.2
V18: D-PWR9.C, PWR9.2
V19: IC20.1, PWR9.1, R-DEV-19.2
V20: D-PWR10.C, PWR10.2
V21: IC22.1, PWR10.1, R-DEV-21.2
V22: D-PWR11.C, PWR11.2
V23: IC24.1, PWR11.1, R-DEV-23.2
V24: D-PWR12.C, PWR12.2
V25: IC26.1, PWR12.1, R-DEV-25.2
V26: D-PWR13.C, PWR13.2
V27: IC28.1, PWR13.1, R-DEV-27.2
V28: D-PWR14.C, PWR14.2
V29: IC30.1, PWR14.1, R-DEV-29.2
V30: D-PWR15.C, PWR15.2
V31: IC32.1, PWR15.1, R-DEV-31.2
VCC: C-PWR-1.+, C-PWR-2.1, DIS1.2, DIS1.15, IC1.4, IC1.6, IC1.18, IC1.20, IC2.3, ISP.1, R-RST.2
VCC1: C-PWR-3.+, C-PWR-4.1, DIS2.2, DIS2.15, IC3.4, IC3.6, IC3.18, IC3.20, IC4.3, ISP1.1, R-RST1.2
VCC2: C-PWR-5.+, C-PWR-6.1, DIS3.2, DIS3.15, IC5.4, IC5.6, IC5.18, IC5.20, IC6.3, ISP2.1, R-RST2.2
VCC3: C-PWR-7.+, C-PWR-8.1, DIS4.2, DIS4.15, IC7.4, IC7.6, IC7.18, IC7.20, IC8.3, ISP3.1, R-RST3.2
VCC4: C-PWR-9.+, C-PWR-10.1, DIS5.2, DIS5.15, IC9.4, IC9.6, IC9.18, IC9.20, IC10.3, ISP4.1, R-RST4.2
VCC5: C-PWR-11.+, C-PWR-12.1, DIS6.2, DIS6.15, IC11.4, IC11.6, IC11.18, IC11.20, IC12.3, ISP5.1, R-RST5.2
VCC6: C-PWR-13.+, C-PWR-14.1, DIS7.2, DIS7.15, IC13.4, IC13.6, IC13.18, IC13.20, IC14.3, ISP6.1, R-RST6.2
VCC7: C-PWR-15.+, C-PWR-16.1, DIS8.2, DIS8.15, IC15.4, IC15.6, IC15.18, IC15.20, IC16.3, ISP7.1, R-RST7.2
VCC8: C-PWR-17.+, C-PWR-18.1, DIS9.2, DIS9.15, IC17.4, IC17.6, IC17.18, IC17.20, IC18.3, ISP8.1, R-RST8.2
VCC9: C-PWR-19.+, C-PWR-20.1, DIS10.2, DIS10.15, IC19.4, IC19.6, IC19.18, IC19.20, IC20.3, ISP9.1, R-RST9.2
VCC10: C-PWR-21.+, C-PWR-22.1, DIS11.2, DIS11.15, IC21.4, IC21.6, IC21.18, IC21.20, IC22.3, ISP10.1, R-RST10.2
VCC11: C-PWR-23.+, C-PWR-24.1, DIS12.2, DIS12.15, IC23.4, IC23.6, IC23.18, IC23.20, IC24.3, ISP11.1, R-RST11.2
VCC12: C-PWR-25.+, C-PWR-26.1, DIS13.2, DIS13.15, IC25.4, IC25.6, IC25.18, IC25.20, IC26.3, ISP12.1, R-RST12.2
VCC13: C-PWR-27.+, C-PWR-28.1, DIS14.2, DIS14.15, IC27.4, IC27.6, IC27.18, IC27.20, IC28.3, ISP13.1, R-RST13.2
VCC14: C-PWR-29.+, C-PWR-30.1, DIS15.2, DIS15.15, IC29.4, IC29.6, IC29.18, IC29.20, IC30.3, ISP14.1, R-RST14.2
VCC15: C-PWR-31.+, C-PWR-32.1, DIS16.2, DIS16.15, IC31.4, IC31.6, IC31.18, IC31.20, IC32.3, ISP15.1, R-RST15.2
